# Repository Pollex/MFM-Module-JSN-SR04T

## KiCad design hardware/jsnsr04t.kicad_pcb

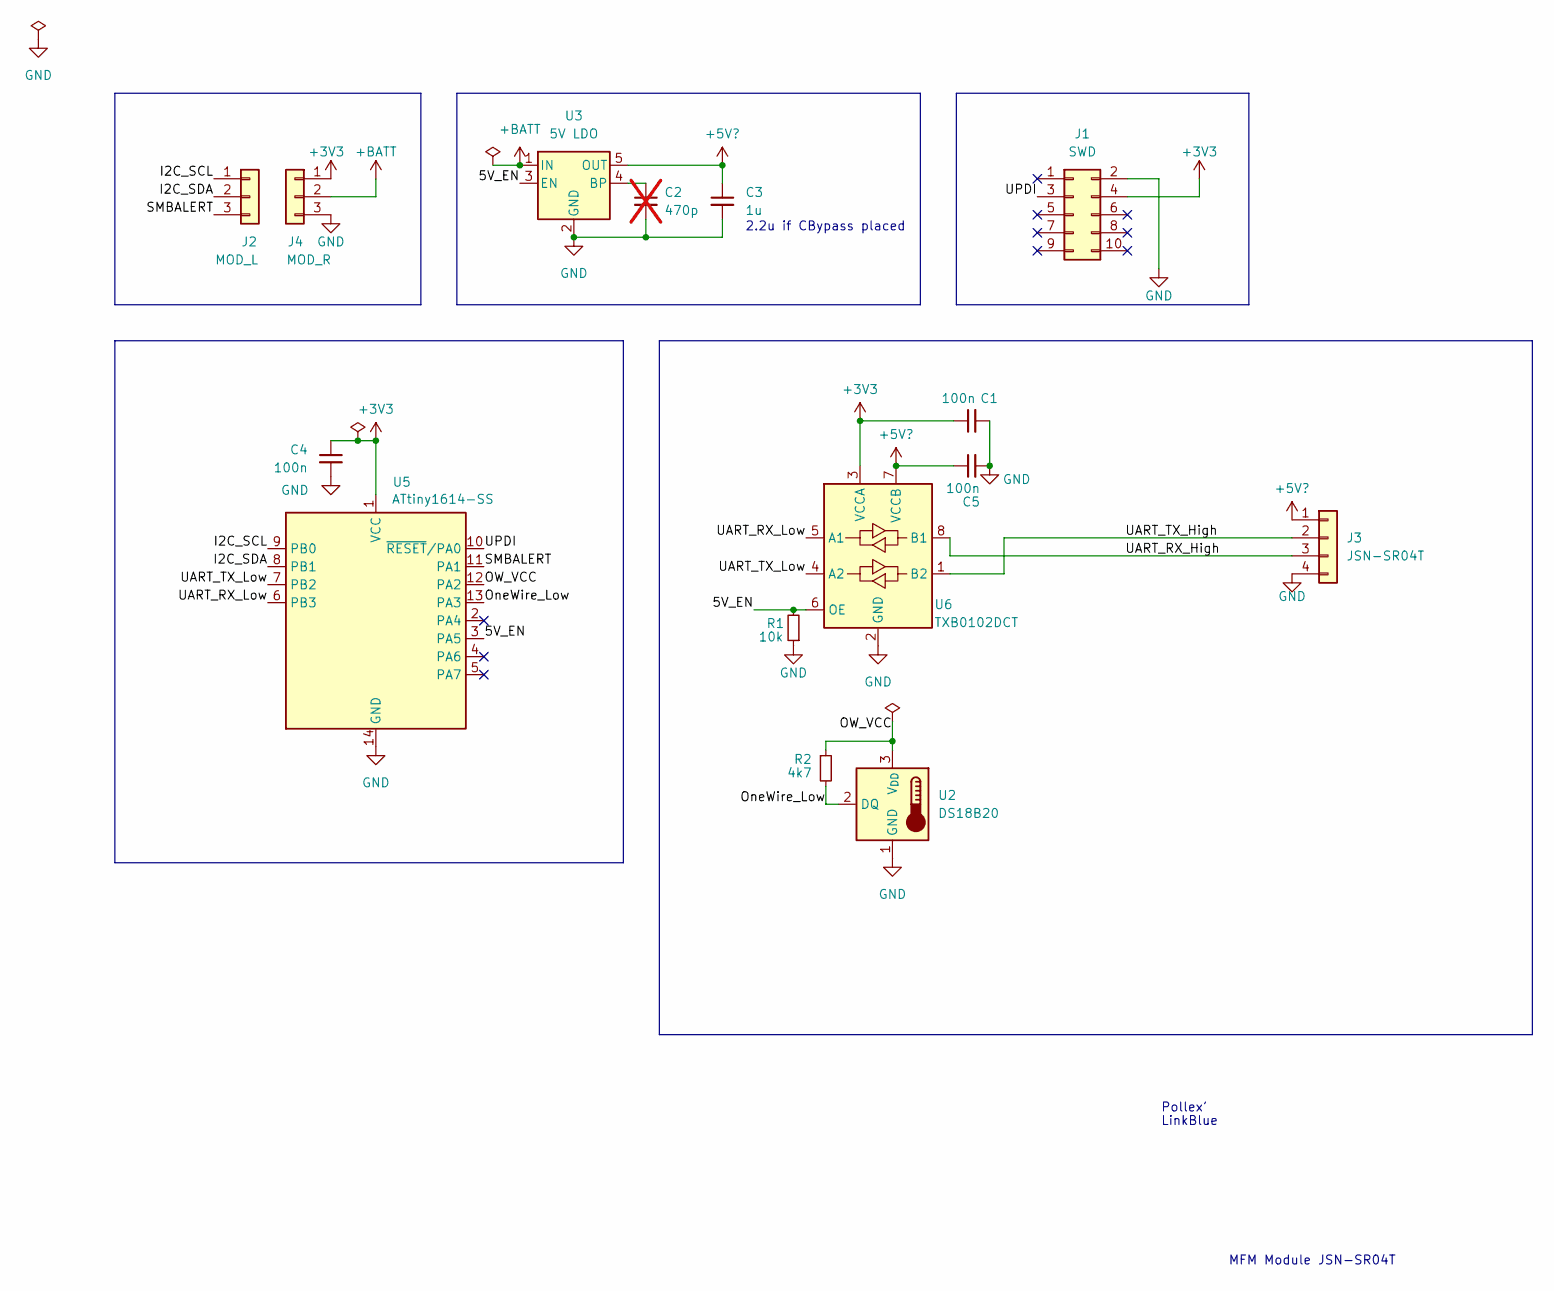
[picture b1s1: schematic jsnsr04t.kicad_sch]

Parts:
C1, C4, C5: 100n; C_0603_1608Metric
C2: 470p; C_0603_1608Metric; not fitted
C3: 1u; C_0603_1608Metric
J1: SWD; Tag-Connect_TC2050-IDC-NL_2x05_P1.27mm_Vertical
J2: MOD_L; PinSocket_1x03_P2.54mm_Vertical
J3: JSN-SR04T; PinHeader_1x04_P2.54mm_Vertical
J4: MOD_R; PinSocket_1x03_P2.54mm_Vertical
R1: 10k; R_0603_1608Metric
R2: 4k7; R_0603_1608Metric
U2: DS18B20; TE-Connectivity_3_pin_terminal_block
U3: 5V LDO; SOT-23-5
U5: ATtiny1614-SS; SOIC-14_3.9x8.7mm_P1.27mm
U6: TXB0102DCT; TSSOP-8_3x3mm_P0.65mm

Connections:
+3V3: C1.1, C4.1, J1.4, J4.1, U5.1 (VCC), U6.3 (VCCA)
+5V?: C3.1, C5.1, J3.1, U3.5 (OUT), U6.7 (VCCB)
+BATT: J4.2, U3.1 (IN)
/5V_EN: R1.2, U3.3 (EN), U5.3 (PA5), U6.6 (OE)
/I2C_SCL: J2.1, U5.9 (PB0)
/I2C_SDA: J2.2, U5.8 (PB1)
/OW_VCC: R2.1, U2.3 (V_{DD}), U5.12 (PA2)
/OneWire_Low: R2.2, U2.2 (DQ), U5.13 (PA3)
/SMBALERT: J2.3, U5.11 (PA1)
/UART_RX_High: J3.3, U6.8 (B1)
/UART_RX_Low: U5.6 (PB3), U6.5 (A1)
/UART_TX_High: J3.2, U6.1 (B2)
/UART_TX_Low: U5.7 (PB2), U6.4 (A2)
/UPDI: J1.3, U5.10 (~RESET/PA0)
GND: C1.2, C2.2, C3.2, C4.2, C5.2, J1.2, J3.4, J4.3, R1.1, U2.1 (GND), U3.2 (GND), U5.14 (GND), U6.2 (GND)
unnamed: C2.1, U3.4 (BP)

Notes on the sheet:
LinkBlue
2.2u if CBypass placed
MFM Module JSN-SR04T
Pollex'

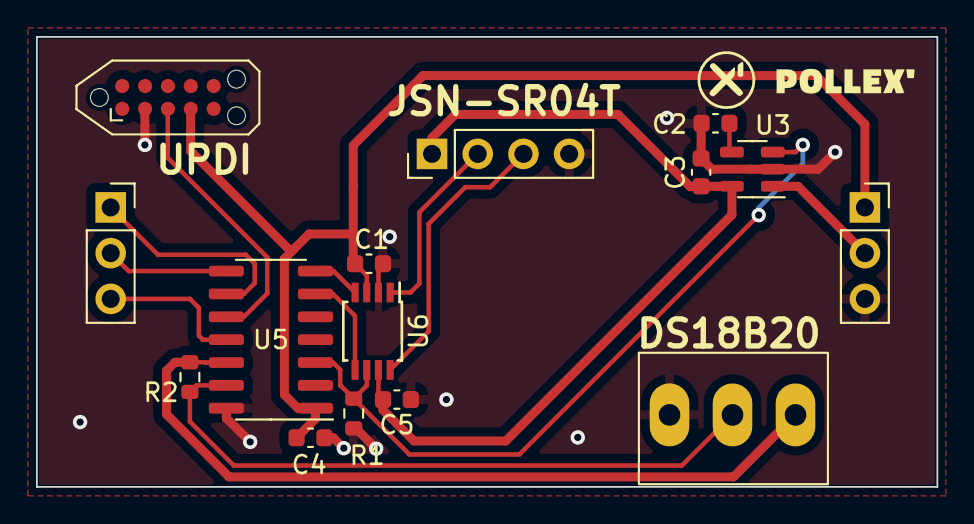
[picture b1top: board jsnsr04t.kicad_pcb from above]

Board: 2 copper layers, 50.0 x 25.0 mm, 15 parts (0 on the bottom side), 16 nets.

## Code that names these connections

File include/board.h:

#if !defined(_BOARD_H_)
#define _BOARD_H_

//
// PIN CONFIG
//
#define ENABLE_5V_PORT PORTA
#define ENABLE_5V_PIN PIN5_bm
#define ENABLE_3V3_PORT PORTA
#define ENABLE_3V3_PIN PIN2_bm

// PORT A
#define SMBALERT_Port PORTA
#define SMBALERT_Pin PIN6_bp
#define DS18B20_PORT PORTA
#define DS18B20_PIN PIN3_bp

// PORT B
#define I2C_Port PORTB
#define I2C_SCL_Pin PIN0_bp
#define I2C_SDA_Pin PIN1_bp

#endif // _BOARD_H_

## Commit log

2023-02-10 Add median filter
2023-03-11 Fix: memcpy causing harfault
2023-12-04 Some update :)?
2023-12-04 Initial v2 design
2023-12-04 Route PCB
2024-01-09 Include terminal blocks for DS18B20
2024-02-01 Drive DS18B20 from IO Port\nRemove DS18B20 from level translator
2024-02-22 Move designator silkscreen
2024-03-26 Update FW pins to latest board design
2024-03-26 refactor(firmware): coreless build
2024-03-26 fix(firmware): DS18B20 Resolution to 11 bit (0.125)
2024-03-26 chore: add build to gitignore
2024-07-30 Fix: extra power saving
2024-07-30 ci(build): add workflow for building firmware
2024-07-30 fix: math include
2024-07-30 ci: add avr-libc to install
2024-07-30 ci: use latest avr-libc by avrdude
2024-07-30 ci: try fix avr libc
2024-07-30 ci: use avr-gcc 14
2024-07-30 ci: fix permissions
2024-07-30 ci: fix loc
2024-07-30 ci: fix missing make
2024-07-31 ci: fix avr-gcc install
2024-07-31 ci: fix wget O
2024-07-31 ci: use ubuntu 24.04
2024-07-31 ci: fix cache
2025-02-17 fix(ds18b20): incorrect temperature calculation
